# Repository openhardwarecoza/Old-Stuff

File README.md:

# Old-Stuff
Just all the old Openhardware.co.za Repos dumped together - archive

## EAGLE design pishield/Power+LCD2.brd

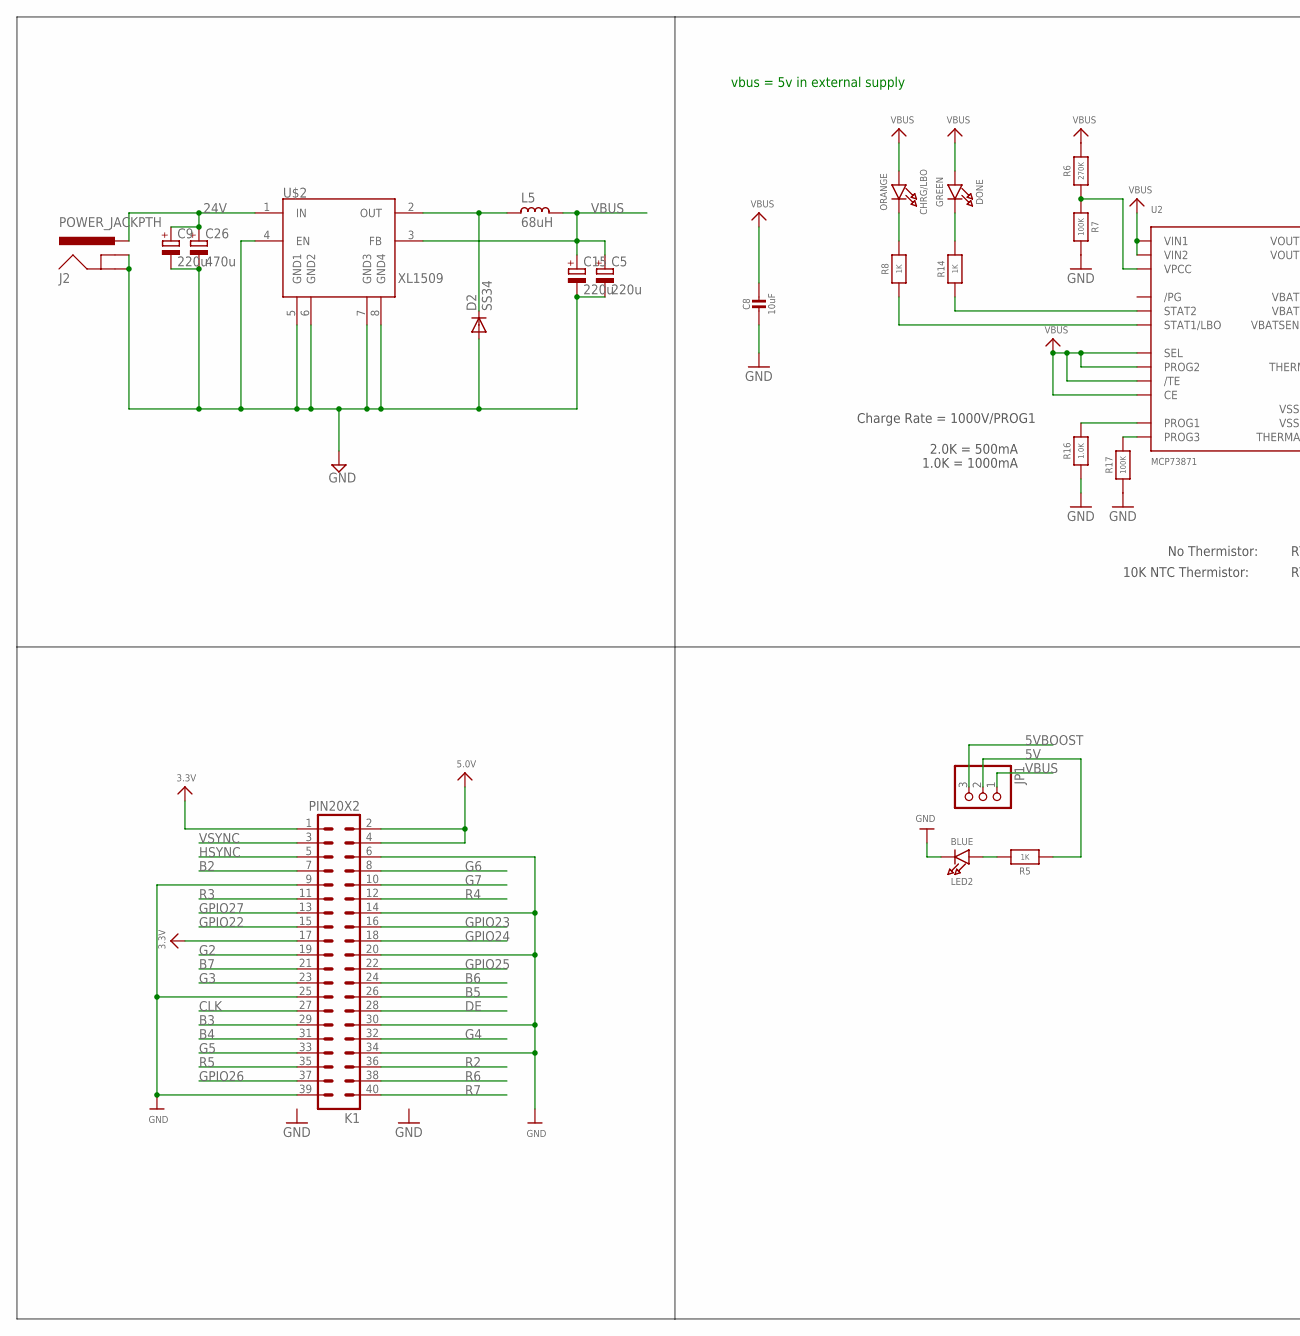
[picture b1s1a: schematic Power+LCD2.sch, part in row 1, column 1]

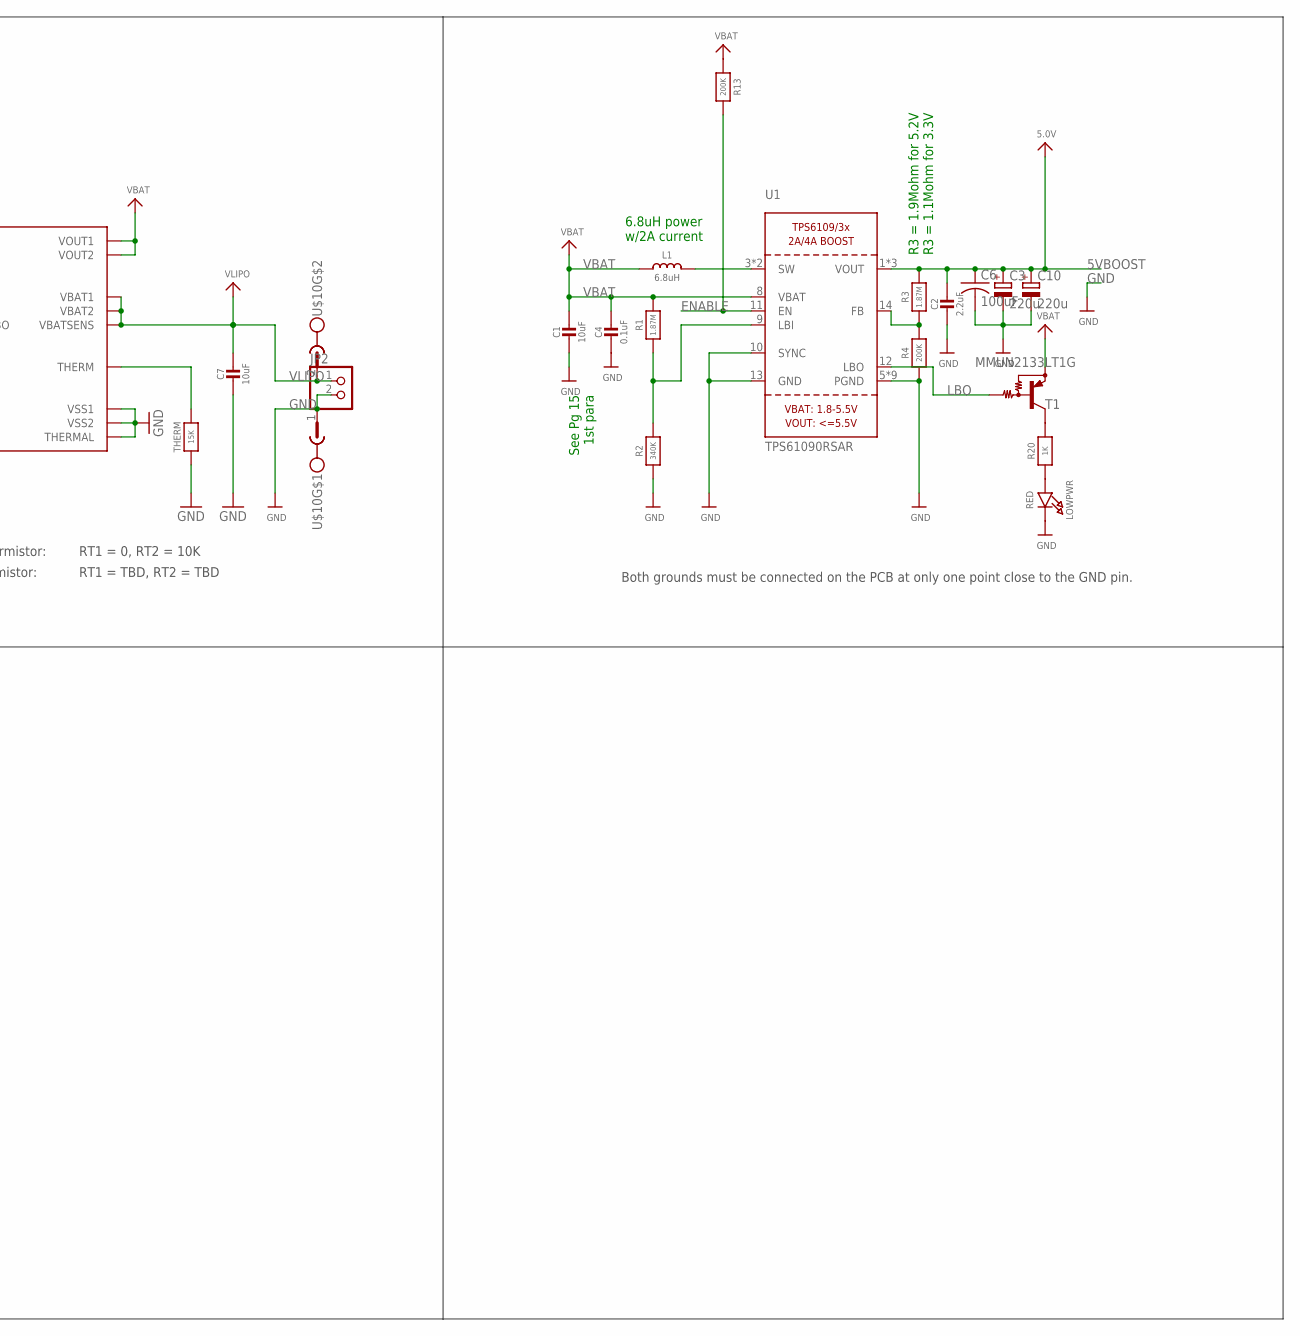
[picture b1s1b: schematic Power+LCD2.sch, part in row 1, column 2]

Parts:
C1, C7, C8: 10uF; _1206MP
C2: 2.2uF; 0805-NO
C3, C15: 220u; E2,5-7
C4: 0.1uF; 0805_10MGAP
C5, C9, C10: 220u; PANASONIC_D
C6: 100uF; C1210
C26: 470u; E2,5-7
CHRG/LBO: ORANGE; CHIPLED_0805_NOOUTLINE
D2: SS34; DO-214AC
DONE: GREEN; CHIPLED_0805_NOOUTLINE
J2: POWER_JACKPTH; POWER_JACK_PTH
JP1: PINHD-1X3; 1X03
JP2: PINHD-1X2; 1X02
K1: PIN20X2; PIN_20X2
L1: 6.8uH; INDUCTOR_5X5MM_TDK_VLC5045
L5: 68uH; CD75
LED2: BLUE; CHIPLED_0805_NOOUTLINE
LOWPWR: RED; CHIPLED_0805_NOOUTLINE
R1: 1.87M; _0805MP
R2: 340K; _0805MP
R3: 1.87M; 0805-NO
R4, R13: 200K; 0805-NO
R5, R8, R14, R20: 1K; 0805-NO
R6: 270K; 0805-NO
R7, R17: 100K; 0805-NO
R16: 1.0K; 0805-NO
T1: MMUN2133LT1G; SC59-BEC
THERM: 15K; 0805-NO
U1: TPS61090RSAR; PVQFN-16
U2: MCP73871; QFN20_4MM
U$2: XL1509; SO08
U$10: MC1.5/2; MC1.5/2-G-3.81

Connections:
3V3: K1.1, K1.17
5V: JP1.2, K1.2, K1.4, R5.1
5VBOOST: C2.1, C3.+, C6.1, C10.+, JP1.3, R3.2, U1.1 (VOUT), U1.15 (VOUT), U1.16 (VOUT)
24V: C9.+, C26.+, J2.PWR, U$2.1 (IN)
B2: K1.7
B3: K1.29
B4: K1.31
B5: K1.26
B6: K1.24
B7: K1.21
CLK: K1.27
DE: K1.28
ENABLE: R13.2, U1.11 (EN)
G2: K1.19
G3: K1.23
G4: K1.32
G5: K1.33
G6: K1.8
G7: K1.10
GND: C1.2, C2.2, C3.-, C4.2, C5.-, C6.2, C7.2, C8.2, C9.-, C10.-, C15.-, C26.-, D2.2 (A), J2.GND, J2.GNDBREAK, JP2.2, K1.6, K1.9, K1.14, K1.20, K1.25, K1.30, K1.34, K1.39, LED2.C, LOWPWR.C, R2.1, R4.1, R7.2, R16.1, R17.1, THERM.1, U1.5 (PGND), U1.6 (PGND), U1.7 (PGND), U1.10 (SYNC), U1.13 (GND), U1.P$18 (PGND), U1.P$19 (PGND), U1.P$20 (PGND), U1.P$21 (PGND), U1.P$22 (PGND), U1.THERMAL (PGND), U2.P$10 (VSS1), U2.P$11 (VSS2), U2.P$21 (THERMAL), U$2.4 (EN), U$2.5 (GND1), U$2.6 (GND2), U$2.7 (GND3), U$2.8 (GND4), U$10.1
GPIO22: K1.15
GPIO23: K1.16
GPIO24: K1.18
GPIO25: K1.22
GPIO26: K1.37
GPIO27: K1.13
HSYNC: K1.5
LBO: T1.B, U1.12 (LBO)
unnamed: L1.P$2 (2), U1.3 (SW), U1.4 (SW)
unnamed: LOWPWR.A, R20.1
unnamed: R1.1, R2.2, U1.9 (LBI)
unnamed: D2.1 (C), L5.2, U$2.2 (OUT)
unnamed: R3.1, R4.2, U1.14 (FB)
unnamed: R20.2, T1.C
unnamed: LED2.A, R5.2
unnamed: R6.1, R7.1, U2.P$2 (VPCC)
unnamed: R14.1, U2.P$7 (STAT2)
unnamed: R16.2, U2.P$13 (PROG1)
unnamed: R8.1, U2.P$8 (STAT1/LBO)
unnamed: THERM.2, U2.P$5 (THERM)
unnamed: DONE.C, R14.2
unnamed: CHRG/LBO.C, R8.2
unnamed: R17.2, U2.P$12 (PROG3)
R2: K1.36
R3: K1.11
R4: K1.12
R5: K1.35
R6: K1.38
R7: K1.40
VBAT: C1.1, C4.1, L1.P$1 (1), R1.2, R13.1, T1.E, U1.8 (VBAT), U2.P$1 (VOUT1), U2.P$20 (VOUT2)
VBUS: C5.+, C8.1, C15.+, CHRG/LBO.A, DONE.A, JP1.1, L5.1, R6.2, U2.P$3 (SEL), U2.P$4 (PROG2), U2.P$9 (/TE), U2.P$17 (CE), U2.P$18 (VIN1), U2.P$19 (VIN2), U$2.3 (FB)
VLIPO: C7.1, JP2.1, U2.P$14 (VBAT1), U2.P$15 (VBAT2), U2.P$16 (VBATSENS), U$10.2
VSYNC: K1.3

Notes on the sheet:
Both grounds must be connected on the PCB at only one point close to the GND pin.
See Pg 15 1st para
6.8uH power w/2A current
R3 = 1.9Mohm for 5.2V R3 = 1.1Mohm for 3.3V
Charge Rate = 1000V/PROG1
1.0K = 1000mA
2.0K = 500mA
No Thermistor:
10K NTC Thermistor:
RT1 = 0, RT2 = 10K
RT1 = TBD, RT2 = TBD
vbus = 5v in external supply

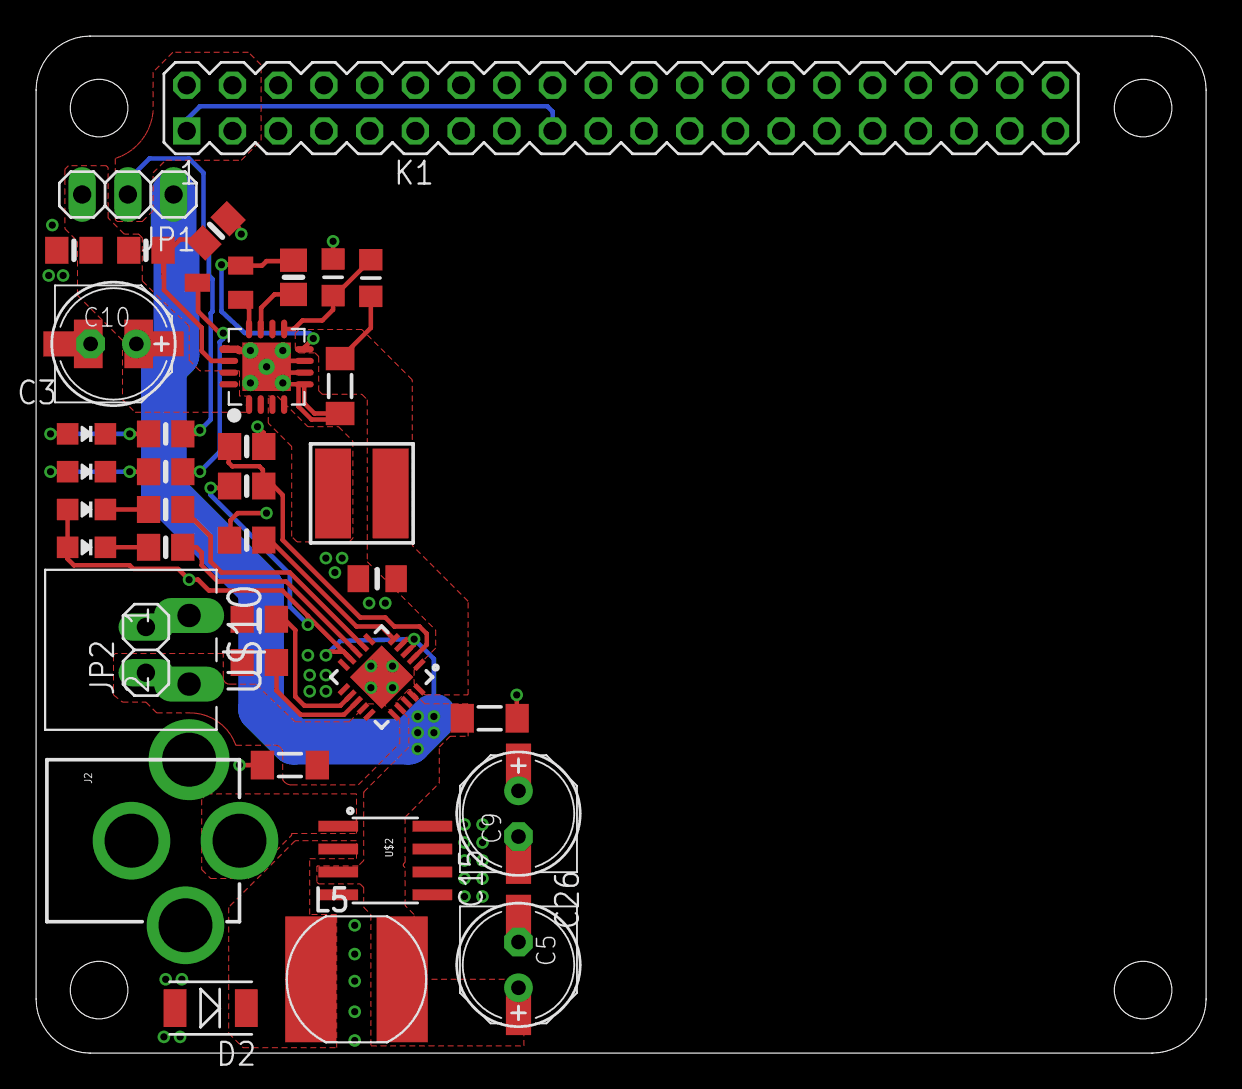
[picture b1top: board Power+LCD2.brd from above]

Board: 2 copper layers, 65.0 x 56.5 mm, 42 parts (0 on the bottom side), 25 nets.

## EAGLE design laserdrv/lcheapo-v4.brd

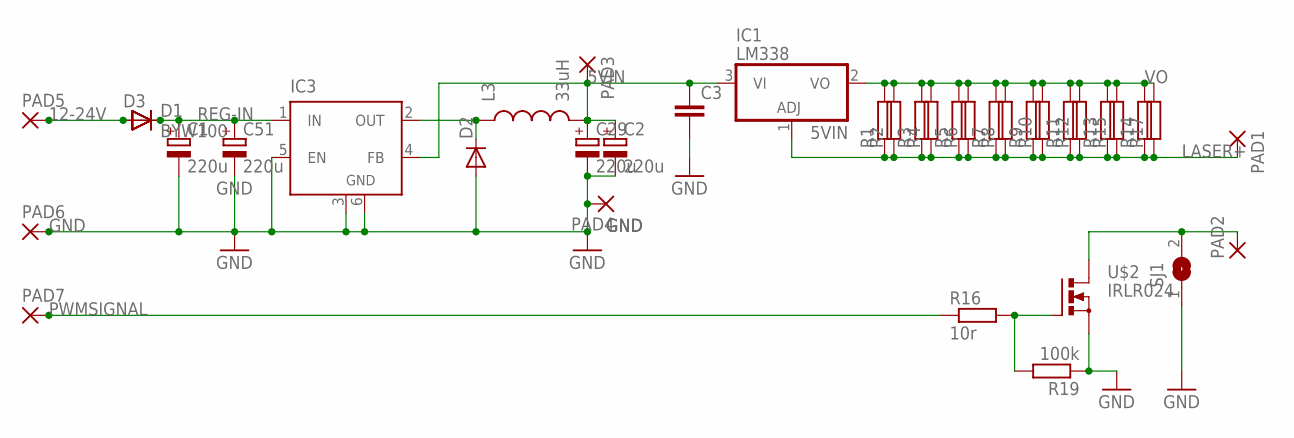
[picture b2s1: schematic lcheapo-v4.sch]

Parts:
C1, C29: 220u; E2,5-7
C2, C51: 220u; PANASONIC_D
C3: C-EUC0603; C0603
D1: BYW100; F126-10
D2: DIODE-DO-214AC; DO-214AC
D3: D-SOD-87; SOD87
IC1: LM338; TO220H
IC3: LM2596S; TO263-5
L3: 33uH; CDRH125
PAD1, PAD2, PAD3, PAD4, PAD7: 2,54/1,0
PAD5, PAD6: 3,17/1,3
R1, R3, R5, R7, R9, R11, R13, R14: R-EU_R2512; R2512
R2, R4, R6, R8, R10, R12, R15, R17: R-EU_0411/3V; 0411V
R16: 10r; R0603
R19: 100k; R0603
SJ1: SJ
U$2: IRLR024; D-PAK_TO252AA

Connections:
2OUT: PAD2.1, SJ1.2, U$2.4 (D)
5VIN: C2.+, C3.1, C29.+, IC1.3 (VI), IC3.4 (FB), L3.2, PAD3.1
12-24V: D1.A, D3.2 (A), PAD5.1
GND: C1.-, C2.-, C3.2, C29.-, C51.-, D2.2 (A), IC3.3 (GND), IC3.5 (EN), IC3.6 (GND), PAD4.1, PAD6.1, R19.1, SJ1.1, U$2.3 (S)
LASER+: IC1.1 (ADJ), PAD1.1, R1.1, R2.1, R3.1, R4.1, R5.1, R6.1, R7.1, R8.1, R9.1, R10.1, R11.1, R12.1, R13.1, R14.1, R15.1, R17.1
unnamed: R16.2, R19.2, U$2.1 (G)
unnamed: D2.1 (C), IC3.2 (OUT), L3.1
PWMSIGNAL: PAD7.1, R16.1
REG-IN: C1.+, C51.+, D1.C, D3.1 (C), IC3.1 (IN)
VO: IC1.2 (VO), R1.2, R2.2, R3.2, R4.2, R5.2, R6.2, R7.2, R8.2, R9.2, R10.2, R11.2, R12.2, R13.2, R14.2, R15.2, R17.2

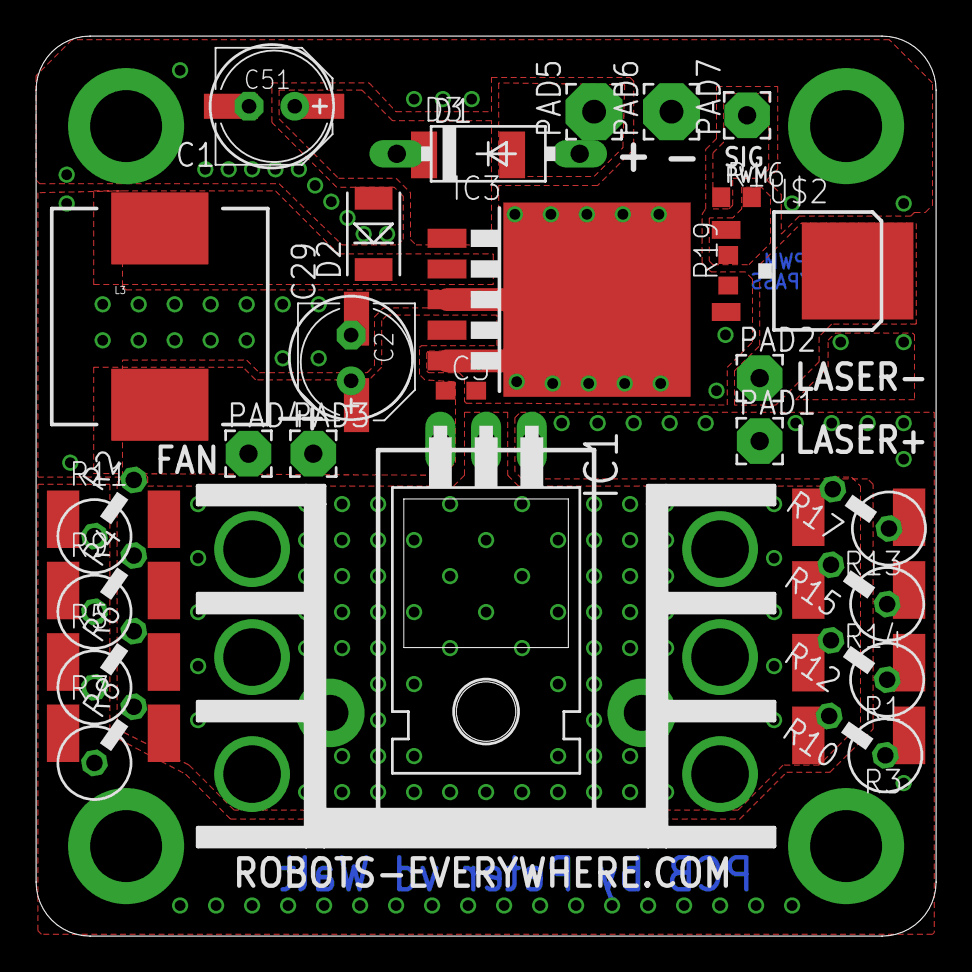
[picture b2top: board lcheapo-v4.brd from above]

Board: 2 copper layers, 50.0 x 50.0 mm, 38 parts (1 on the bottom side), 10 nets.

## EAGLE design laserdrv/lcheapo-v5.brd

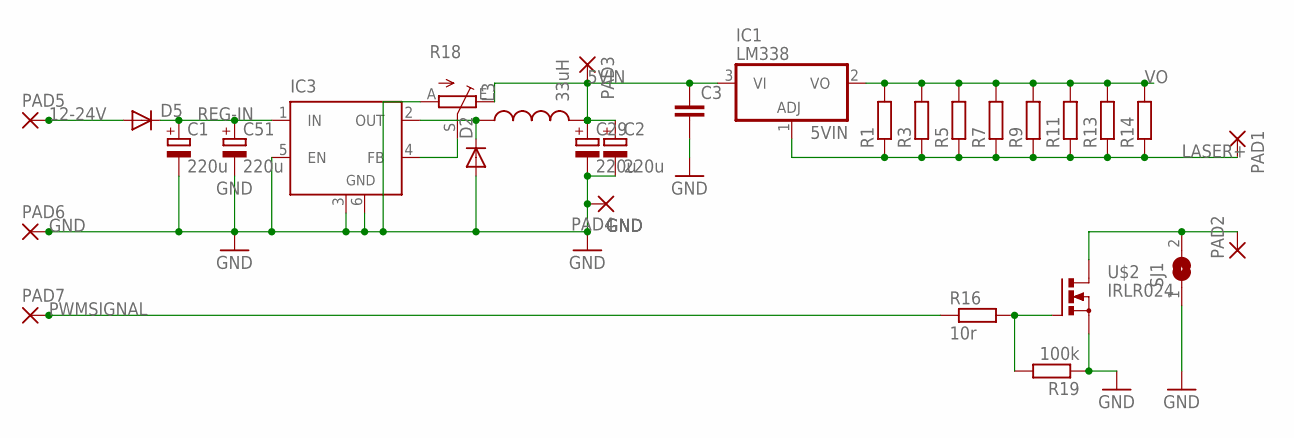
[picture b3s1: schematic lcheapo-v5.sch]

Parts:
C1, C29: 220u; E2,5-7
C2, C51: 220u; PANASONIC_D
C3: C-EUC0603; C0603
D2: DIODE-DO-214AC; DO-214AC
D5: DIODE-MELF-MLL41; MELF-MLL41
IC1: LM338; TO220H
IC3: LM2596S; TO263-5
L3: 33uH; CDRH125
PAD1, PAD2, PAD3, PAD4: 2,54/1,0
PAD5, PAD6, PAD7: 2,54/1,1
R1, R3, R5, R7, R9, R11, R13, R14: R-EU_R2512; R2512
R16: 10r; R1206
R18: TRIM_EU-RJ9W; RJ9W
R19: 100k; R1206
SJ1: SJ
U$2: IRLR024; D-PAK_TO252AA

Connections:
2OUT: PAD2.1, SJ1.2, U$2.4 (D)
5VIN: C2.+, C3.1, C29.+, IC1.3 (VI), L3.2, PAD3.1, R18.E
12-24V: D5.A, PAD5.1
FEEDBACK: IC3.4 (FB), R18.S
GND: C1.-, C2.-, C3.2, C29.-, C51.-, D2.2 (A), IC3.3 (GND), IC3.5 (EN), IC3.6 (GND), PAD4.1, PAD6.1, R18.A, R19.1, SJ1.1, U$2.3 (S)
LASER+: IC1.1 (ADJ), PAD1.1, R1.1, R3.1, R5.1, R7.1, R9.1, R11.1, R13.1, R14.1
unnamed: R16.2, R19.2, U$2.1 (G)
unnamed: D2.1 (C), IC3.2 (OUT), L3.1
PWMSIGNAL: PAD7.1, R16.1
REG-IN: C1.+, C51.+, D5.C, IC3.1 (IN)
VO: IC1.2 (VO), R1.2, R3.2, R5.2, R7.2, R9.2, R11.2, R13.2, R14.2

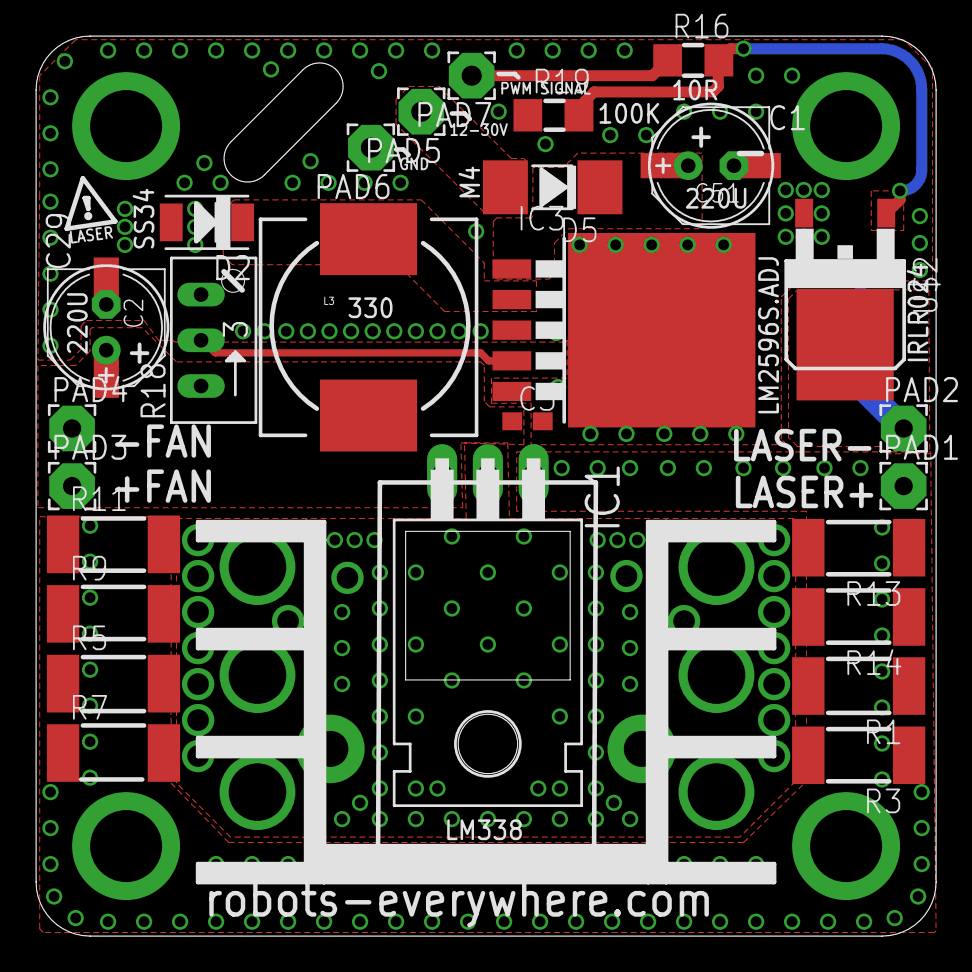
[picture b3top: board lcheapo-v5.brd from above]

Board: 2 copper layers, 50.0 x 50.0 mm, 30 parts (1 on the bottom side), 11 nets.

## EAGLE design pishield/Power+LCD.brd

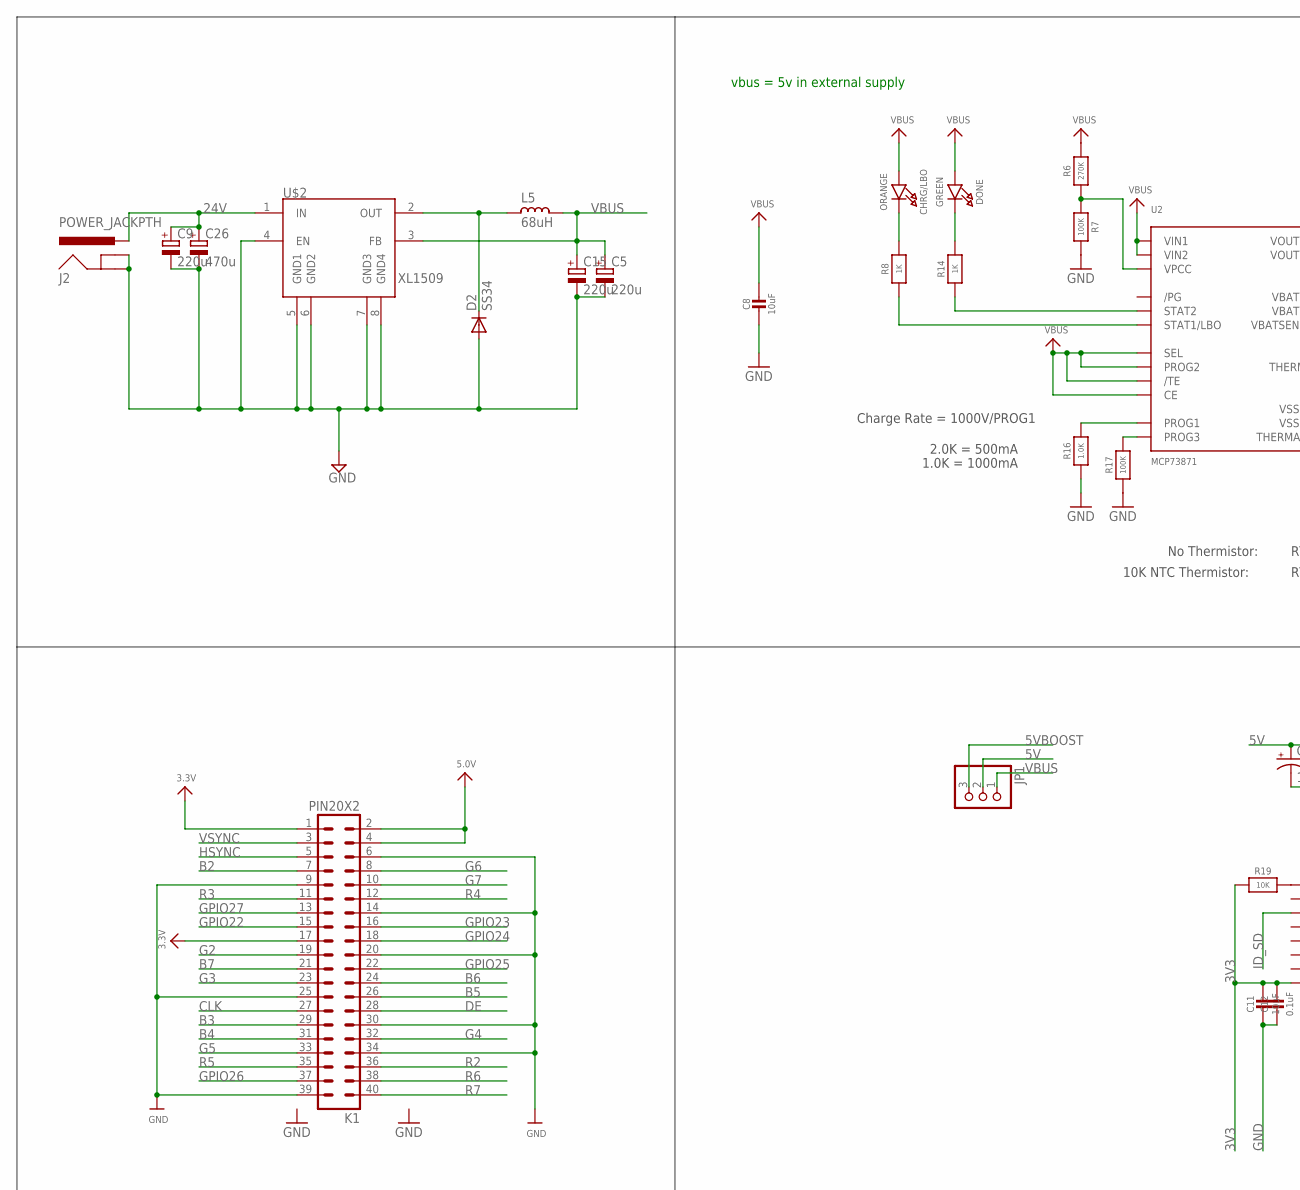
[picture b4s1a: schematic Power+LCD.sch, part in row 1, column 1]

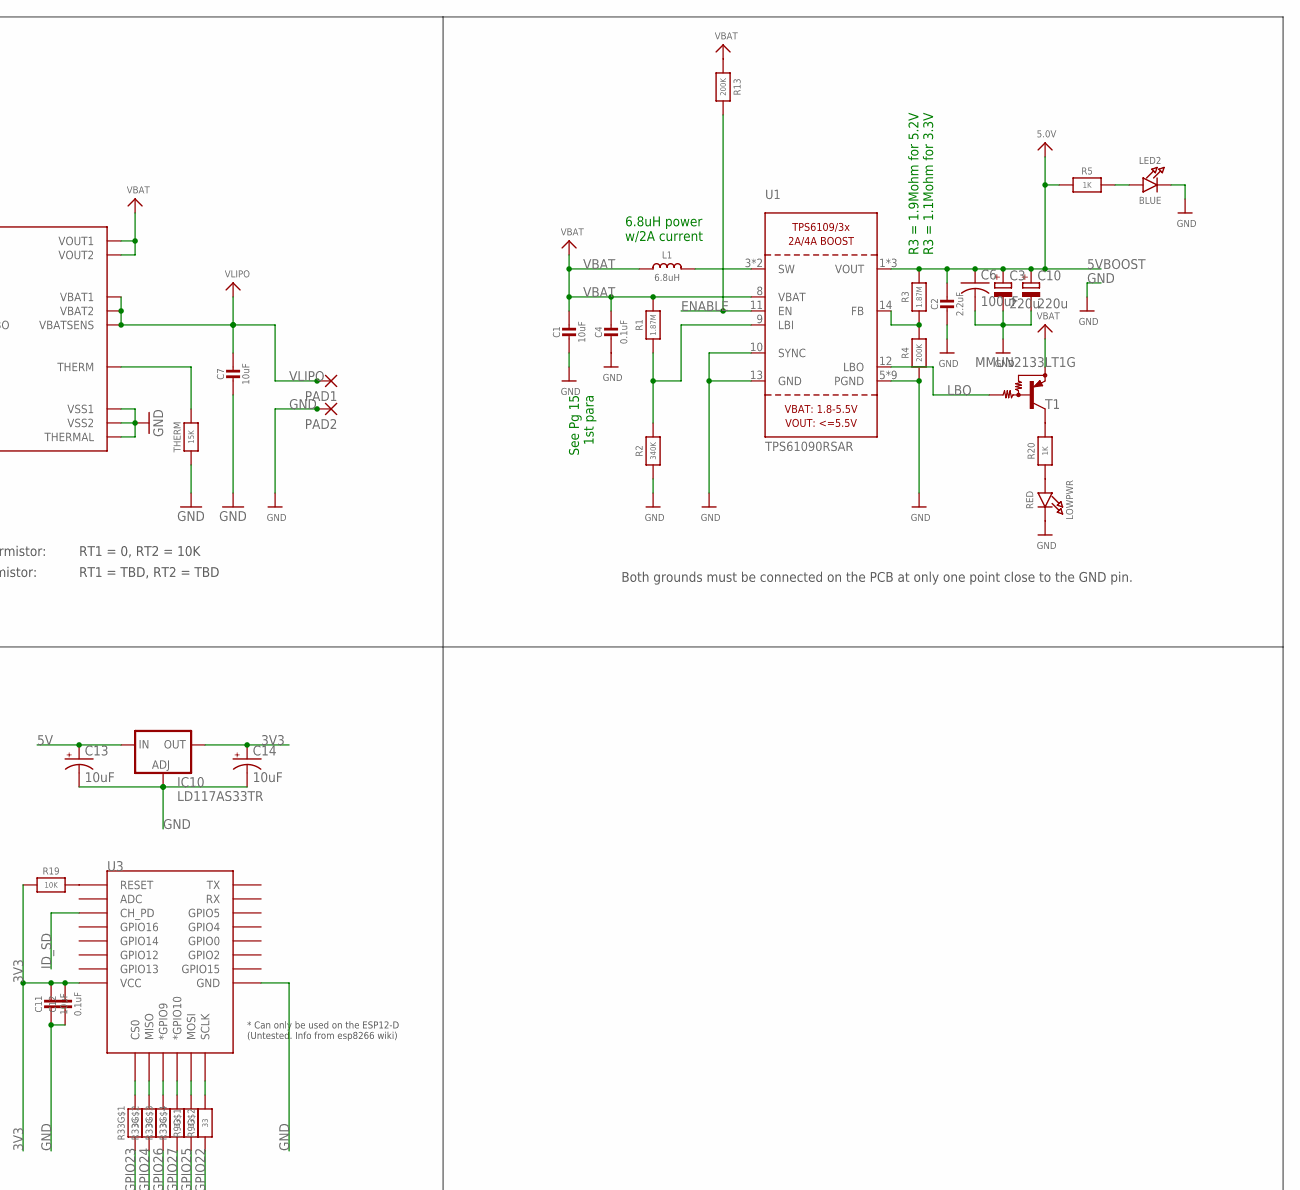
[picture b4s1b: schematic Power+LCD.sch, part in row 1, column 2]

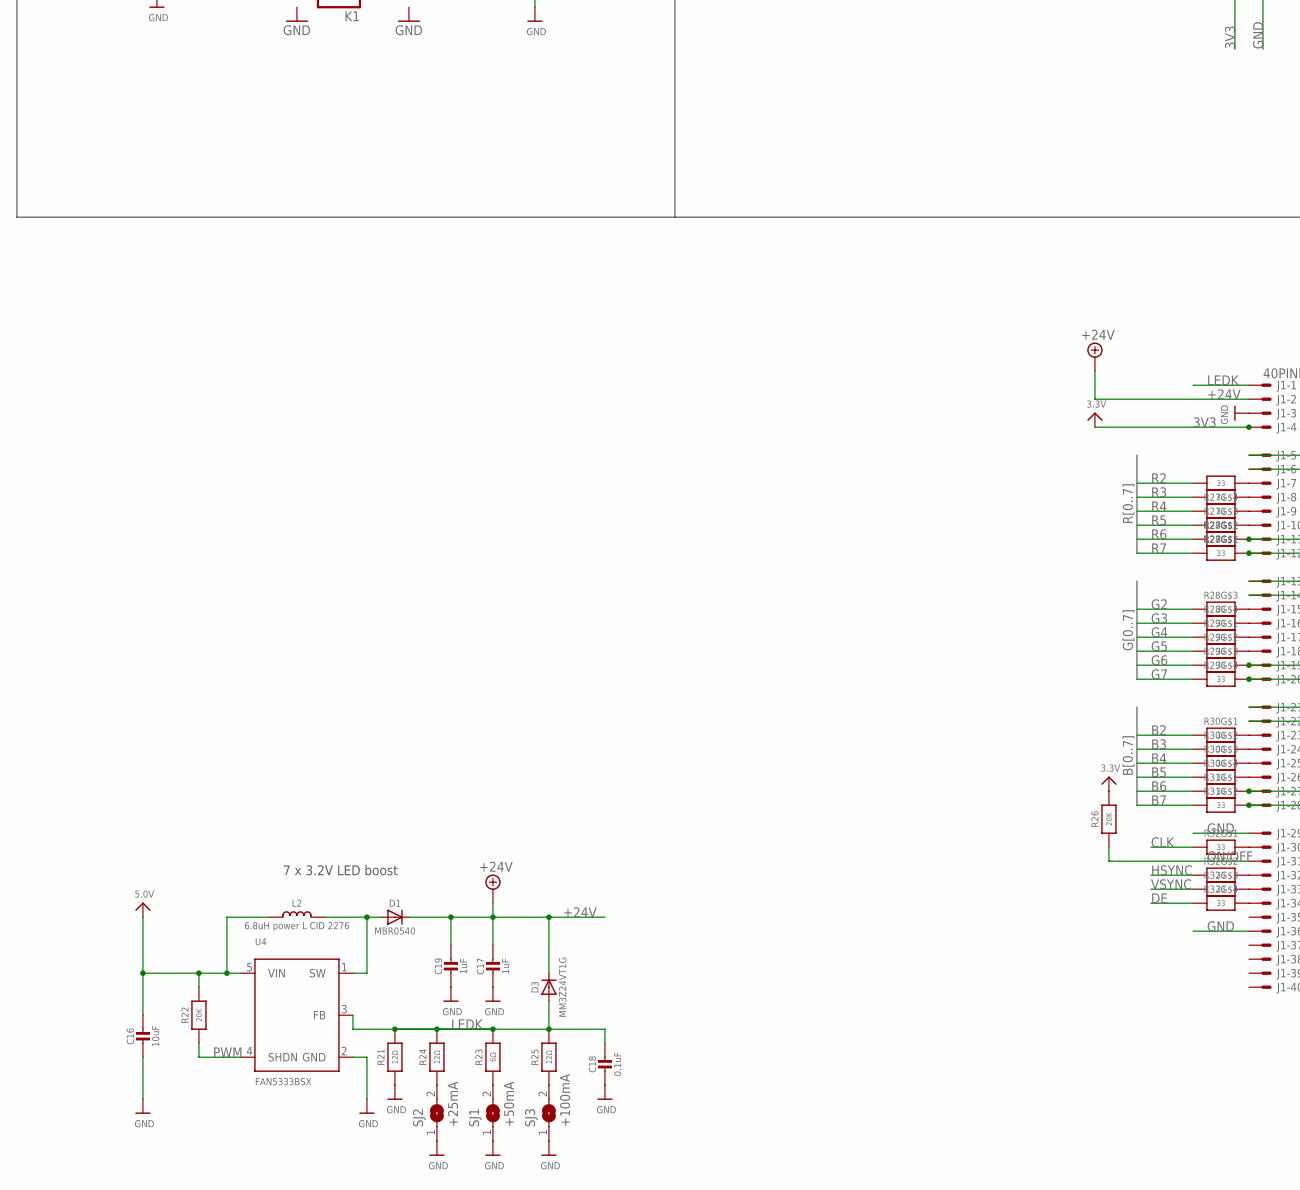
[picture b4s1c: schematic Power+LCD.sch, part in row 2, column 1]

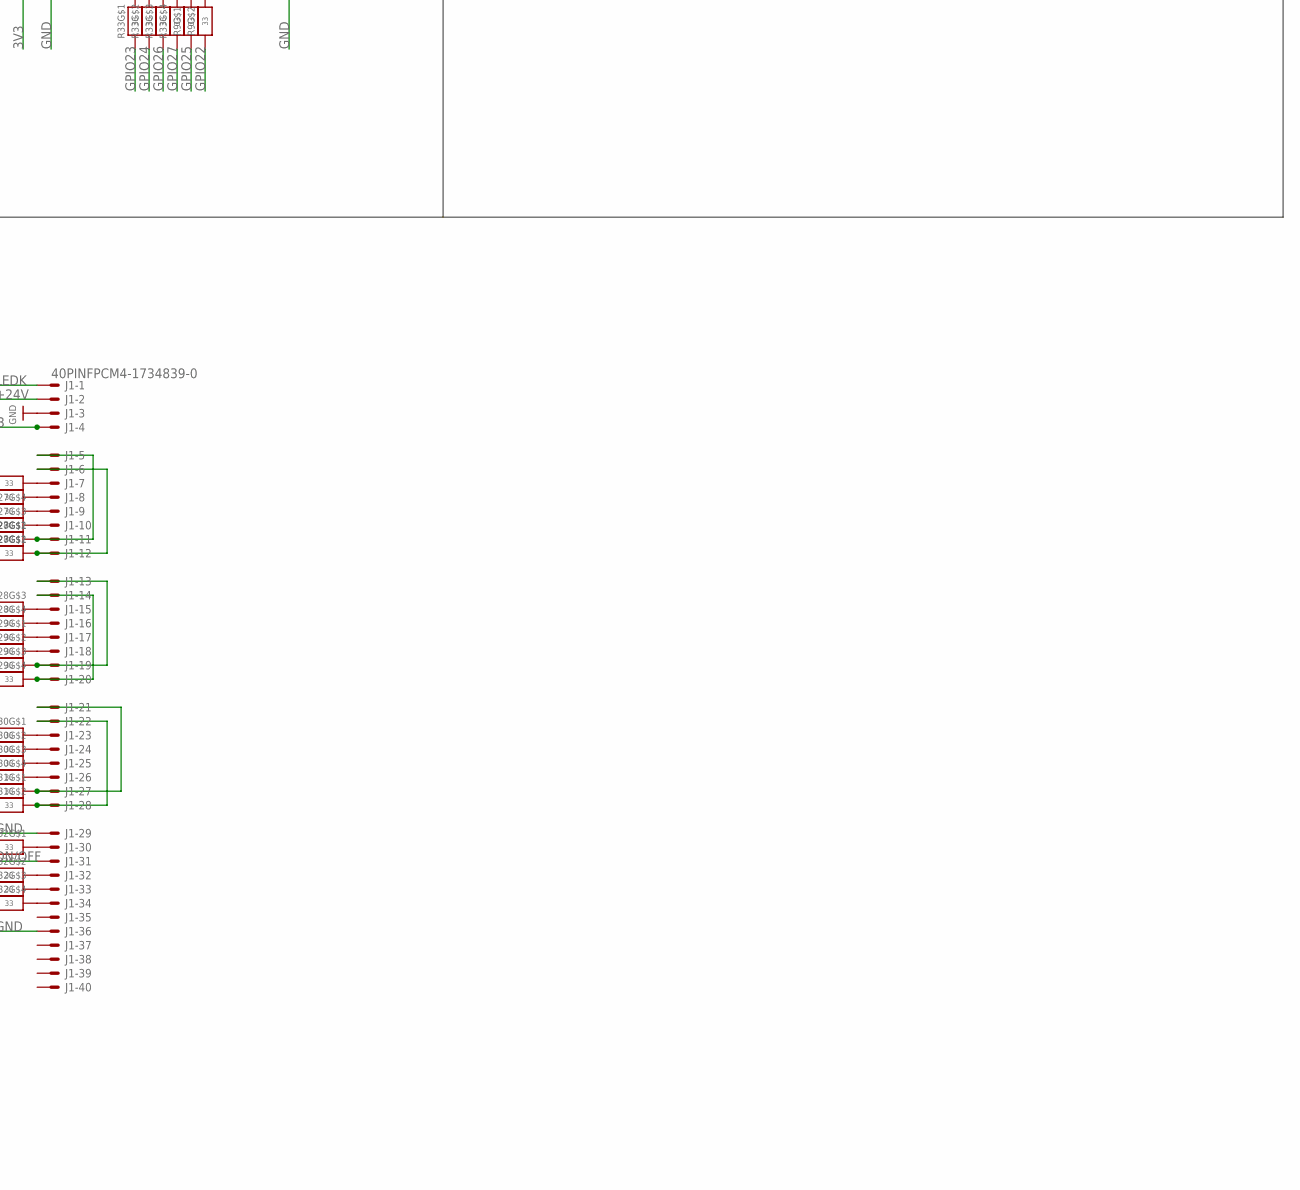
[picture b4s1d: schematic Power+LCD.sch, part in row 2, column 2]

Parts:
C1, C7, C8, C11, C16: 10uF; _1206MP
C2: 2.2uF; 0805-NO
C3, C15: 220u; E2,5-7
C4, C12: 0.1uF; 0805_10MGAP
C5, C9, C10: 220u; PANASONIC_D
C6: 100uF; C1210
C13, C14: 10uF; EIA3216
C17, C19: 1uF; _0805MP
C18: 0.1uF; 0805-NO
C26: 470u; E2,5-7
CHRG/LBO: ORANGE; CHIPLED_0805_NOOUTLINE
D1: MBR0540; SOD-123
D2: SS34; DO-214AC
D3: MM3Z24VT1G; SMADIODE
DONE: GREEN; CHIPLED_0805_NOOUTLINE
IC10: LD117AS33TR; SOT223
J1: 40PINFPCM4-1734839-0; 4-1734839-0
J2: POWER_JACKPTH; POWER_JACK_PTH
JP1: PINHD-1X3; 1X03
K1: PIN20X2; PIN_20X2
L1: 6.8uH; INDUCTOR_5X5MM_TDK_VLC5045
L2: 6.8uH power L CID 2276; INDUCTOR_5X5MM_NR5040_NOTHERMALS
L5: 68uH; CD75
LED2: BLUE; CHIPLED_0805_NOOUTLINE
LOWPWR: RED; CHIPLED_0805_NOOUTLINE
PAD1, PAD2: 3,81/1,4
R1: 1.87M; _0805MP
R2: 340K; _0805MP
R3: 1.87M; 0805-NO
R4, R13: 200K; 0805-NO
R5, R8, R14, R20: 1K; 0805-NO
R6: 270K; 0805-NO
R7, R17: 100K; 0805-NO
R9, R27, R28, R29, R30, R31, R32, R33: 33; RESPACK_4X0603
R16: 1.0K; 0805-NO
R19: 10K; 0805-NO
R21, R24, R25: 12Ω; 0805-NO
R22: 20K; 0805-NO
R23: 6Ω; 0805-NO
R26: 20K; _0805MP
SJ1: +50mA; SOLDERJUMPER_ARROW_NOPASTE
SJ2: +25mA; SOLDERJUMPER_ARROW_NOPASTE
SJ3: +100mA; SOLDERJUMPER_ARROW_NOPASTE
T1: MMUN2133LT1G; SC59-BEC
THERM: 15K; 0805-NO
U1: TPS61090RSAR; PVQFN-16
U2: MCP73871; QFN20_4MM
U3: ESP12ESMD; ESP12E-SMD
U4: FAN5333BSX; SOT23-5@1
U$2: XL1509; SO08

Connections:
3V3: C11.1, C12.1, C14.A (+), IC10.4 (OUT), J1.4 (MS), K1.1, K1.17, R19.1, R26.2, U3.VCC
5V: C13.A (+), C16.1, IC10.3 (IN), JP1.2, K1.2, K1.4, L2.P$1 (1), R22.2, U4.5 (VIN)
5VBOOST: C2.1, C3.+, C6.1, C10.+, JP1.3, R3.2, R5.1, U1.1 (VOUT), U1.15 (VOUT), U1.16 (VOUT)
24V: C9.+, C26.+, J2.PWR, U$2.1 (IN)
+24V: C17.1, C19.1, D1.C, D3.C, J1.2 (MS)
B2: K1.7, R30.1
B3: K1.29, R30.2 (1)
B4: K1.31, R30.3 (1)
B5: K1.26, R30.4 (1)
B6: K1.24, R31.1
B7: K1.21, R31.2 (1)
CLK: K1.27, R32.1
DE: K1.28, R32.4 (1)
ENABLE: R13.2, U1.11 (EN)
G2: K1.19, R28.3 (1)
G3: K1.23, R28.4 (1)
G4: K1.32, R29.1
G5: K1.33, R29.2 (1)
G6: K1.8, R29.3 (1)
G7: K1.10, R29.4 (1)
GND: C1.2, C2.2, C3.-, C4.2, C5.-, C6.2, C7.2, C8.2, C9.-, C10.-, C11.2, C12.2, C13.C (-), C14.C (-), C15.-, C16.2, C17.2, C18.2, C19.2, C26.-, D2.2 (A), IC10.1 (ADJ), J1.3 (MS), J1.29 (MS), J1.36 (MS), J2.GND, J2.GNDBREAK, K1.6, K1.9, K1.14, K1.20, K1.25, K1.30, K1.34, K1.39, LED2.C, LOWPWR.C, PAD2.1, R2.1, R4.1, R7.2, R16.1, R17.1, R21.1, SJ1.1, SJ2.1, SJ3.1, THERM.1, U1.5 (PGND), U1.6 (PGND), U1.7 (PGND), U1.10 (SYNC), U1.13 (GND), U1.P$18 (PGND), U1.P$19 (PGND), U1.P$20 (PGND), U1.P$21 (PGND), U1.P$22 (PGND), U1.THERMAL (PGND), U2.P$10 (VSS1), U2.P$11 (VSS2), U2.P$21 (THERMAL), U3.GND, U4.2 (GND), U$2.4 (EN), U$2.5 (GND1), U$2.6 (GND2), U$2.7 (GND3), U$2.8 (GND4)
GPIO22: K1.15, R9.2 (1)
GPIO23: K1.16, R33.1
GPIO24: K1.18, R33.2 (1)
GPIO25: K1.22, R9.1
GPIO26: K1.37, R33.3 (1)
GPIO27: K1.13, R33.4 (1)
HSYNC: K1.5, R32.2 (1)
ID_SD: U3.CH_PD
LBO: T1.B, U1.12 (LBO)
LEDK: C18.1, D3.A, J1.1 (MSV), R21.2, R23.2, R24.2, R25.2, U4.3 (FB)
unnamed: L1.P$2 (2), U1.3 (SW), U1.4 (SW)
unnamed: LOWPWR.A, R20.1
unnamed: R1.1, R2.2, U1.9 (LBI)
unnamed: D2.1 (C), L5.2, U$2.2 (OUT)
unnamed: R3.1, R4.2, U1.14 (FB)
unnamed: R20.2, T1.C
unnamed: LED2.A, R5.2
unnamed: R6.1, R7.1, U2.P$2 (VPCC)
unnamed: R14.1, U2.P$7 (STAT2)
unnamed: R16.2, U2.P$13 (PROG1)
unnamed: R8.1, U2.P$8 (STAT1/LBO)
unnamed: R9.7 (2), U3.SCLK
unnamed: R9.8 (2), U3.MOSI
unnamed: R33.5 (2), U3.GPIO10 (*GPIO10)
unnamed: R33.6 (2), U3.GPIO9 (*GPIO9)
unnamed: R33.7 (2), U3.MISO
unnamed: R33.8 (2), U3.CS0
unnamed: D1.A, L2.P$2 (2), U4.1 (SW)
unnamed: THERM.2, U2.P$5 (THERM)
unnamed: DONE.C, R14.2
unnamed: CHRG/LBO.C, R8.2
unnamed: R17.2, U2.P$12 (PROG3)
unnamed: R23.1, SJ1.2
unnamed: R24.1, SJ2.2
unnamed: R19.2, U3.RESET
unnamed: R25.1, SJ3.2
unnamed: J1.6 (MS), J1.12 (MS), R28.7 (2)
unnamed: J1.5 (MS), J1.11 (MS), R28.8 (2)
unnamed: J1.10 (MS), R27.1
unnamed: J1.9 (MS), R27.2 (1)
unnamed: J1.8 (MS), R27.3 (1)
unnamed: J1.7 (MS), R27.4 (1)
unnamed: J1.15 (MS), R28.6 (2)
unnamed: J1.16 (MS), R28.5 (2)
unnamed: J1.17 (MS), R29.8 (2)
unnamed: J1.18 (MS), R29.7 (2)
unnamed: J1.13 (MS), J1.19 (MS), R29.6 (2)
unnamed: J1.14 (MS), J1.20 (MS), R29.5 (2)
unnamed: J1.23 (MS), R30.8 (2)
unnamed: J1.24 (MS), R30.7 (2)
unnamed: J1.25 (MS), R30.6 (2)
unnamed: J1.26 (MS), R30.5 (2)
unnamed: J1.21 (MS), J1.27 (MS), R31.8 (2)
unnamed: J1.22 (MS), J1.28 (MS), R31.7 (2)
unnamed: J1.30 (MS), R32.8 (2)
unnamed: J1.32 (MS), R32.7 (2)
unnamed: J1.33 (MS), R32.6 (2)
unnamed: J1.34 (MS), R32.5 (2)
ON/OFF: J1.31 (MS), R26.1
PWM: R22.1, U4.4 (SHDN)
R2: K1.36, R27.5 (2)
R3: K1.11, R27.6 (2)
R4: K1.12, R27.7 (2)
R5: K1.35, R27.8 (2)
R6: K1.38, R28.1
R7: K1.40, R28.2 (1)
VBAT: C1.1, C4.1, L1.P$1 (1), R1.2, R13.1, T1.E, U1.8 (VBAT), U2.P$1 (VOUT1), U2.P$20 (VOUT2)
VBUS: C5.+, C8.1, C15.+, CHRG/LBO.A, DONE.A, JP1.1, L5.1, R6.2, U2.P$3 (SEL), U2.P$4 (PROG2), U2.P$9 (/TE), U2.P$17 (CE), U2.P$18 (VIN1), U2.P$19 (VIN2), U$2.3 (FB)
VLIPO: C7.1, PAD1.1, U2.P$14 (VBAT1), U2.P$15 (VBAT2), U2.P$16 (VBATSENS)
VSYNC: K1.3, R32.3 (1)

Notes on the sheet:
Both grounds must be connected on the PCB at only one point close to the GND pin.
See Pg 15 1st para
6.8uH power w/2A current
R3 = 1.9Mohm for 5.2V R3 = 1.1Mohm for 3.3V
Charge Rate = 1000V/PROG1
1.0K = 1000mA
2.0K = 500mA
No Thermistor:
10K NTC Thermistor:
RT1 = 0, RT2 = 10K
RT1 = TBD, RT2 = TBD
vbus = 5v in external supply
7 x 3.2V LED boost

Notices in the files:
parts and their libraries:
SparkFun-DiscreteSemi: Licensing: CC v3.0 Share-Alike You are welcome to use this library for commercial purposes.
rc-master-smd: Copyright (C) 2007, Bob Starr
SparkFun-Connectors: Licensing: Creative Commons ShareAlike 4.0 International - https://creativecommons.org/licenses/by-sa/4.0
